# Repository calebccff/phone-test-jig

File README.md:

# OnePlus 6 Test Jig

The OnePlus 6 test jig is a proof of concept designed to turn the OnePlus 6 into a device which can be used in a board farm!

The PCB contains a header at the top for soldering wires onto test points on the phone, it features an Atmega32u4 which can act as a
UART<->USB adapter, an LSF0102 bidirectional logic level voltage translator to convert the UART from the 5v of the Atmega down to the
1.8v of the phone (and vice versa).

The Atmega is also used to simulate button presses on the phone, the volume and power button test pads are normally high and pressed when low.
Both of these features can be (though as yet untested) exposed via the same USB port, saving a port on the host and allowing for dirt simple 
control of the device, to test the inputs as well as perform a hard reset.

Being able to hard reset the board is a requirement for consideration in an automated board farm, this carried some complications on the OnePlus 6
as if you perform a hard reset combination (pressing volume up and power at the same time for 10 seconds) whilst VBUS (USB power) is high it will 
boot into EDL mode instead, so without a way to control VBUS the device would just be stuck in EDL. This is resolved by using a high-side FQP27P06
MOSFET.

> **NOTE:** Currently waiting for PCB shipment, expect this design to contain bugs.

## TODO

* Create a list of minimum hard requirements for a given device to be used as part of the farm
* Add a 12v connector and buck regulator to produce VBAT for devices which support it so that the batteries can be removed.
* Add PHONE_USB passthrough port so that devices without USB test points can still have VBUS be controlled by the atmega

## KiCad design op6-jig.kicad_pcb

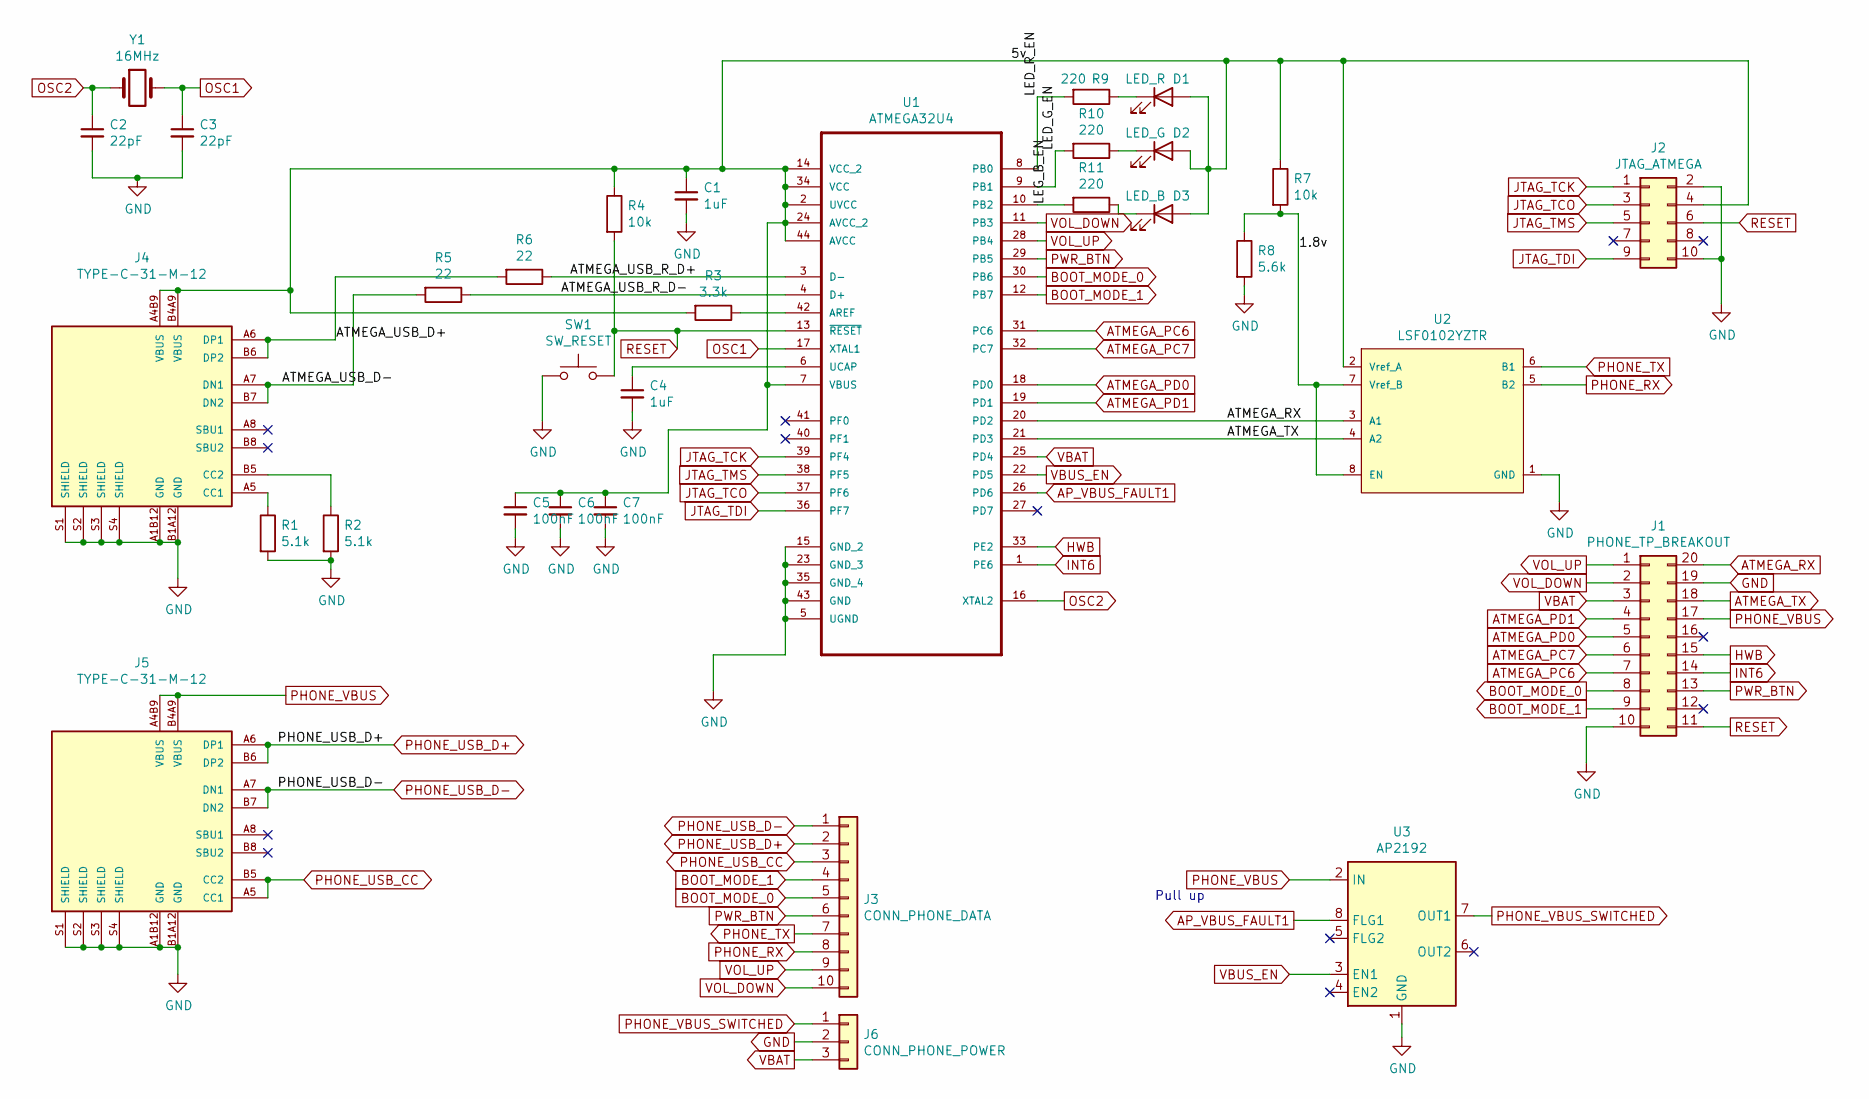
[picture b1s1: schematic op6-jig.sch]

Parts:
C1, C4: 1uF; C_0805_2012Metric; LCSC C28323
C2, C3: 22pF; C_0805_2012Metric; LCSC C1804
C5, C6, C7: 100nF; C_0805_2012Metric; LCSC C49678
D1: LED_R; LED_1206_3216Metric; LCSC C84256
D2: LED_G; LED_1206_3216Metric; LCSC C2297
D3: LED_B; LED_1206_3216Metric; LCSC C2297
J1: PHONE_TP_BREAKOUT; PinHeader_2x10_P2.54mm_Vertical
J2: JTAG_ATMEGA; PinHeader_2x05_P2.54mm_Vertical
J3: CONN_PHONE_DATA; PinHeader_1x10_P2.54mm_Vertical
J4, J5: TYPE-C-31-M-12; HRO_TYPE-C-31-M-12; LCSC C17414
J6: CONN_PHONE_POWER; PinHeader_1x03_P2.54mm_Vertical
R1, R2: 5.1k; R_0805_2012Metric; LCSC C27834
R3: 3.3k; R_0805_2012Metric; LCSC C26010
R4, R7: 10k; R_0805_2012Metric; LCSC C22859
R5, R6: 22; R_0805_2012Metric; LCSC C17561
R8: 5.6k; R_0805_2012Metric; LCSC C4382
R9, R10, R11: 220; R_0805_2012Metric; LCSC C17557
SW1: SW_RESET; SW_PUSH_6mm
U1: ATMEGA32U4; ATmega32U4
U2: LSF0102YZTR; VSSOP-8_2.4x2.1mm_P0.5mm; mouser part number 595-LSF0102YZTR; digikey description IC LEVEL TRANSLATOR BIDIR 8BGA
U3: AP2192; SO-8_3.9x4.9mm_P1.27mm; LCSC C155322
Y1: 16MHz; Crystal_HC18-U_Vertical

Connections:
/1.8v: R7.2, R8.1, U2.7 (Vref_B), U2.8 (EN)
/5v: C1.1, C5.1, C6.1, C7.1, D1.2 (A), D2.2 (A), D3.2 (A), J2.4, J4.A4B9 (VBUS), J4.B4A9 (VBUS), R3.2, R4.1, R7.1, U1.2 (UVCC), U1.7 (VBUS), U1.14 (VCC_2), U1.24 (AVCC_2), U1.34 (VCC), U1.44 (AVCC), U2.2 (Vref_A)
/ATMEGA_USB_D+: J4.A6 (DP1), J4.B6 (DP2), R6.2
/ATMEGA_USB_D-: J4.A7 (DN1), J4.B7 (DN2), R5.2
/ATMEGA_USB_R_D+: R6.1, U1.3 (D-)
/ATMEGA_USB_R_D-: R5.1, U1.4 (D+)
/LED_G_EN: R10.2, U1.9 (PB1)
/LED_R_EN: R9.2, U1.8 (PB0)
/LEG_B_EN: R11.2, U1.10 (PB2)
AP_VBUS_FAULT1: U1.26 (PD6), U3.8 (FLG1)
ATMEGA_PC6: J1.7, U1.31 (PC6)
ATMEGA_PC7: J1.6, U1.32 (PC7)
ATMEGA_PD0: J1.5, U1.18 (PD0)
ATMEGA_PD1: J1.4, U1.19 (PD1)
ATMEGA_RX: J1.20, U1.20 (PD2), U2.3 (A1)
ATMEGA_TX: J1.18, U1.21 (PD3), U2.4 (A2)
BOOT_MODE_0: J1.8, J3.5, U1.30 (PB6)
BOOT_MODE_1: J1.9, J3.4, U1.12 (PB7)
GND: C1.2, C2.2, C3.2, C4.2, C5.2, C6.2, C7.2, J1.10, J1.19, J2.2, J2.10, J4.A1B12 (GND), J4.B1A12 (GND), J4.S1 (SHIELD), J4.S2 (SHIELD), J4.S3 (SHIELD), J4.S4 (SHIELD), J5.A1B12 (GND), J5.B1A12 (GND), J5.S1 (SHIELD), J5.S2 (SHIELD), J5.S3 (SHIELD), J5.S4 (SHIELD), J6.2, R1.2, R2.2, R8.2, SW1.1, U1.5 (UGND), U1.15 (GND_2), U1.23 (GND_3), U1.35 (GND_4), U1.43 (GND), U2.1 (GND), U3.1 (GND)
HWB: J1.15, U1.33 (PE2)
INT6: J1.14, U1.1 (PE6)
JTAG_TCK: J2.1, U1.39 (PF4)
JTAG_TCO: J2.3, U1.37 (PF6)
JTAG_TDI: J2.9, U1.36 (PF7)
JTAG_TMS: J2.5, U1.38 (PF5)
unnamed: C4.1, U1.6 (UCAP)
unnamed: D1.1 (K), R9.1
unnamed: D2.1 (K), R10.1
unnamed: D3.1 (K), R11.1
unnamed: J4.A5 (CC1), R1.1
unnamed: J4.B5 (CC2), R2.1
unnamed: R3.1, U1.42 (AREF)
OSC1: C3.1, U1.17 (XTAL1), Y1.2
OSC2: C2.1, U1.16 (XTAL2), Y1.1
PHONE_RX: J3.8, U2.5 (B2)
PHONE_TX: J3.7, U2.6 (B1)
PHONE_USB_CC: J3.3, J5.A5 (CC1), J5.B5 (CC2)
PHONE_USB_D+: J3.2, J5.A6 (DP1), J5.B6 (DP2)
PHONE_USB_D-: J3.1, J5.A7 (DN1), J5.B7 (DN2)
PHONE_VBUS: J1.17, J5.A4B9 (VBUS), J5.B4A9 (VBUS), U3.2 (IN)
PHONE_VBUS_SWITCHED: J6.1, U3.7 (OUT1)
PWR_BTN: J1.13, J3.6, U1.29 (PB5)
RESET: J1.11, J2.6, R4.2, SW1.2, U1.13 (~RESET)
VBAT: J1.3, J6.3, U1.25 (PD4)
VBUS_EN: U1.22 (PD5), U3.3 (EN1)
VOL_DOWN: J1.2, J3.10, U1.11 (PB3)
VOL_UP: J1.1, J3.9, U1.28 (PB4)

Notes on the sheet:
Pull up

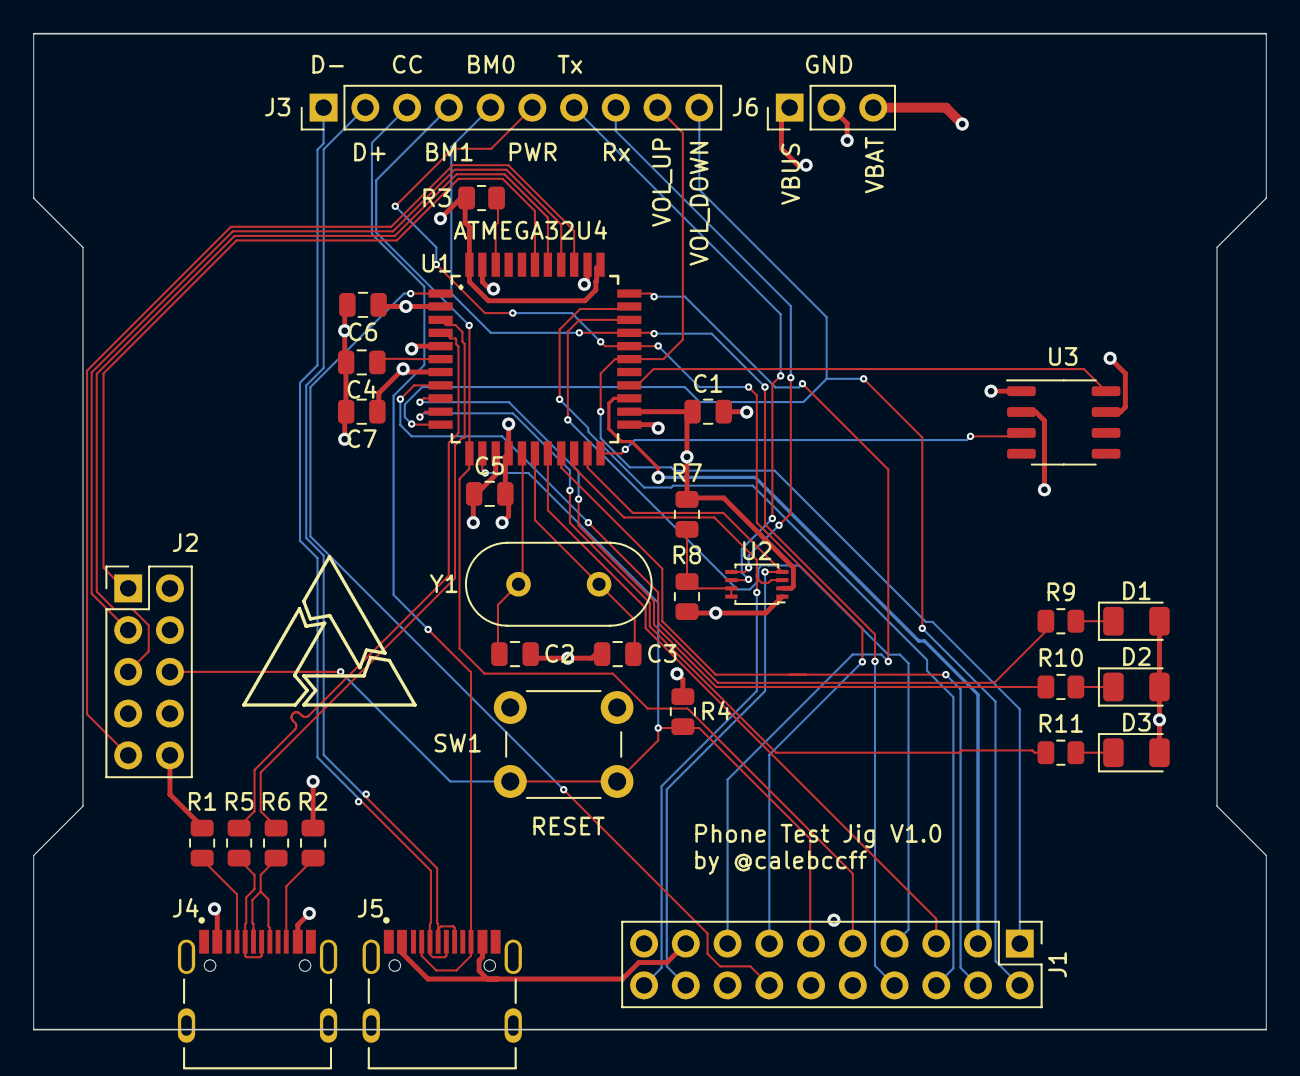
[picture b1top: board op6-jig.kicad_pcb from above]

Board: 4 copper layers, 75.0 x 60.6 mm, 32 parts (0 on the bottom side), 47 nets.

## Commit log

2021-08-31 Jig v1.0
2021-08-31 Add README
2021-08-31 README: Add TODO
2021-08-31 PCB: fix missing trace :C
2021-09-23 pcb: rewire by hand
    hah, i actually did it...
    The PCB is now hand wired and muuuuuuuch better. This drops the USB pins
    on the breakout header because they probably aren't needed and added too
    much complexity to the traces.
    Also replace the UART pinout with the 5v one on the Atmega side of the
    level shifter rather than the 1.8v levels at the phone.
2021-09-24 PCB: improve some routing
    Less vias = more good :D
2021-09-24 update screenshot
2021-09-24 some minor fixes
2021-09-27 updates, ready-er to produce?
    * Replaced the mosfet with a switching IC (thanks @A13).
    * Removed ATMEGA MISC header, put those pins on the general 20-pin
    header.
    * Replaced USB-C part with a better SMD part (thanks again @A13).
    * Some misc fixes / routing improvements.
2021-09-29 Final-final-v2.docx (it's ordered)
    - Replaced the precisely positioned and probably wrong test points with
    a pin header connector which can just be soldered too.
    - Cleaned up some traces, resized all vias to be a minimum of 0.45mm for
    JLCPCB.
    - Ordered the board!
2021-09-30 fix some cap spacing
2021-09-30 LICENCE: Licence under GPLv3
2021-09-30 README: update image URL for sr.ht
2021-09-30 README: updates
2021-09-30 ci: add sourcehut ci
2021-09-30 ci: add kibot config and builds
    CI now generates production files ready to submit to JLCPCB
2021-09-30 ci: fixes
    kibot ci works, github ci now force pushes :D
2022-02-14 uhhh
